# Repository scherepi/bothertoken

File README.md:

# bothertoken
A simple little PCB toy designed for Hack Club's Solder YSWS. 

This little design uses an NPN transistor, a photoresistor, and a SPST switch to bother all your friends endlessly. When switched on and placed in an environment with low light (like your friend's bag) it'll buzz utilizing the vibrating motor until turned off or brought into light. The light sensitivity can be adjusted using the potentiometer.

## Bill of Materials:
- Cell Battery
- Photoresistor
- Resistor
- Potentiometer
- NPN Transistor
- Vibrating DC Motor

-----
*My slack username is **guac md**.*

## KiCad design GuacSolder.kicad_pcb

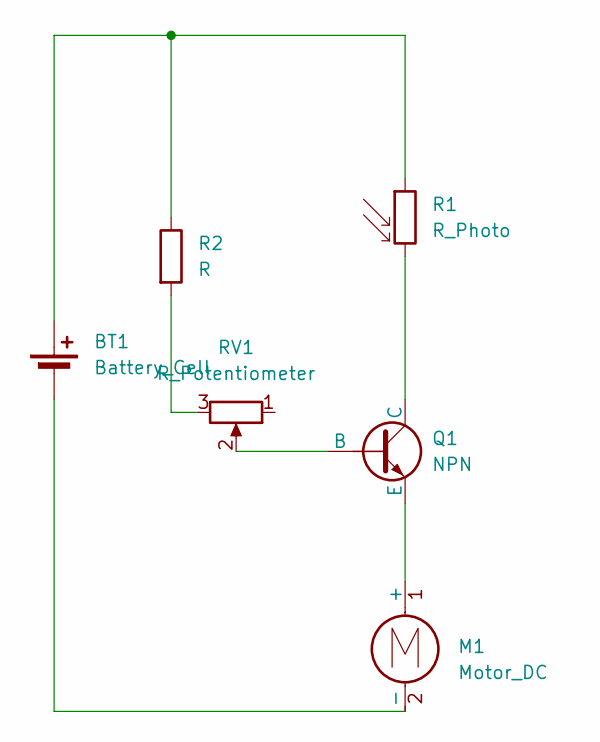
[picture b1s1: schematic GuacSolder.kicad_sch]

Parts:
BT1: Battery_Cell; BatteryHolder_Keystone_3034_1x20mm
M1: Motor_DC; PinHeader_1x02_P2.54mm_Vertical
Q1: NPN; TO-92L_HandSolder
R1: R_Photo; R_LDR_4.9x4.2mm_P2.54mm_Vertical
R2: R; R_Axial_DIN0207_L6.3mm_D2.5mm_P7.62mm_Horizontal
RV1: R_Potentiometer; Potentiometer_Vishay_T73YP_Vertical

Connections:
unnamed: BT1.1 (+), R1.1, R2.1
unnamed: BT1.2 (-), M1.2 (-)
unnamed: M1.1 (+), Q1.3 (E)
unnamed: Q1.2 (B), RV1.2
unnamed: Q1.1 (C), R1.2
unnamed: R2.2, RV1.3

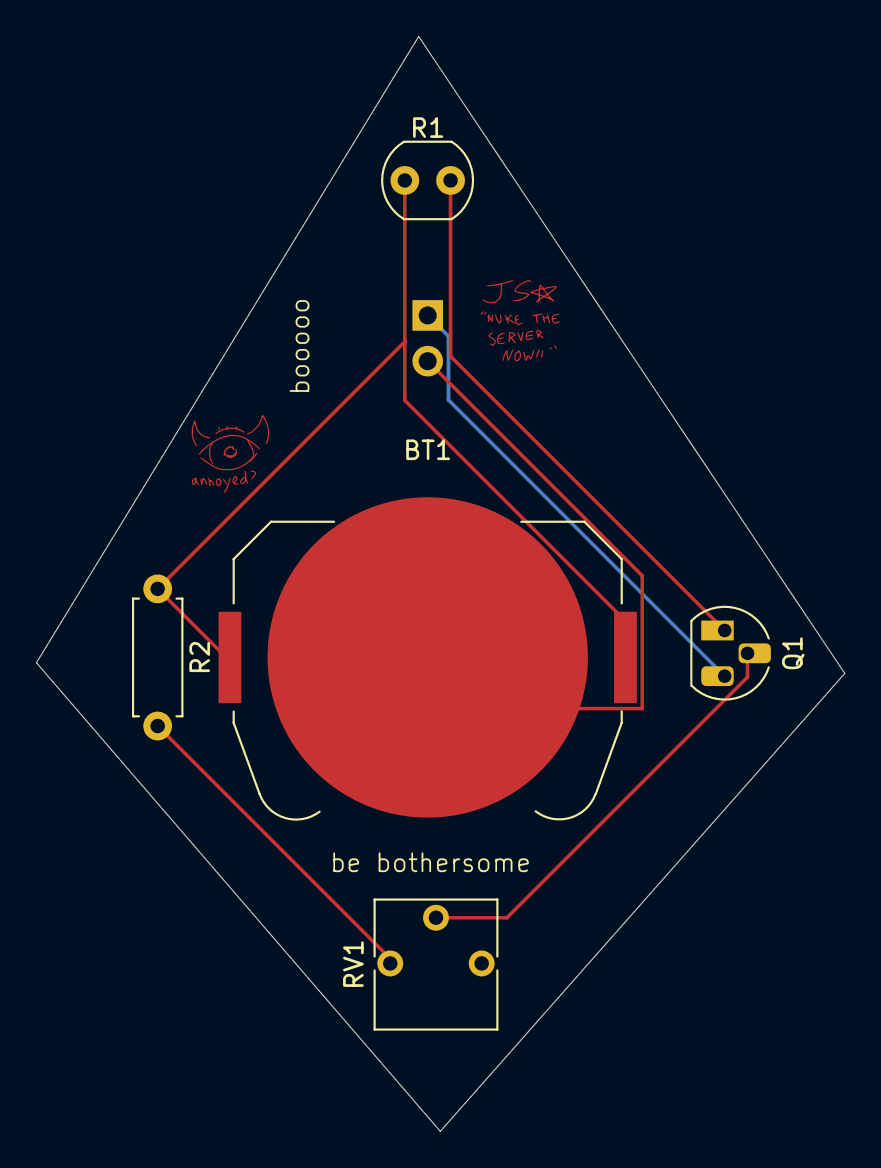
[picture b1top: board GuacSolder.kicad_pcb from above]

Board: 2 copper layers, 44.9 x 60.8 mm, 6 parts (1 on the bottom side), 6 nets.

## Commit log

2025-05-02 Uploaded files
